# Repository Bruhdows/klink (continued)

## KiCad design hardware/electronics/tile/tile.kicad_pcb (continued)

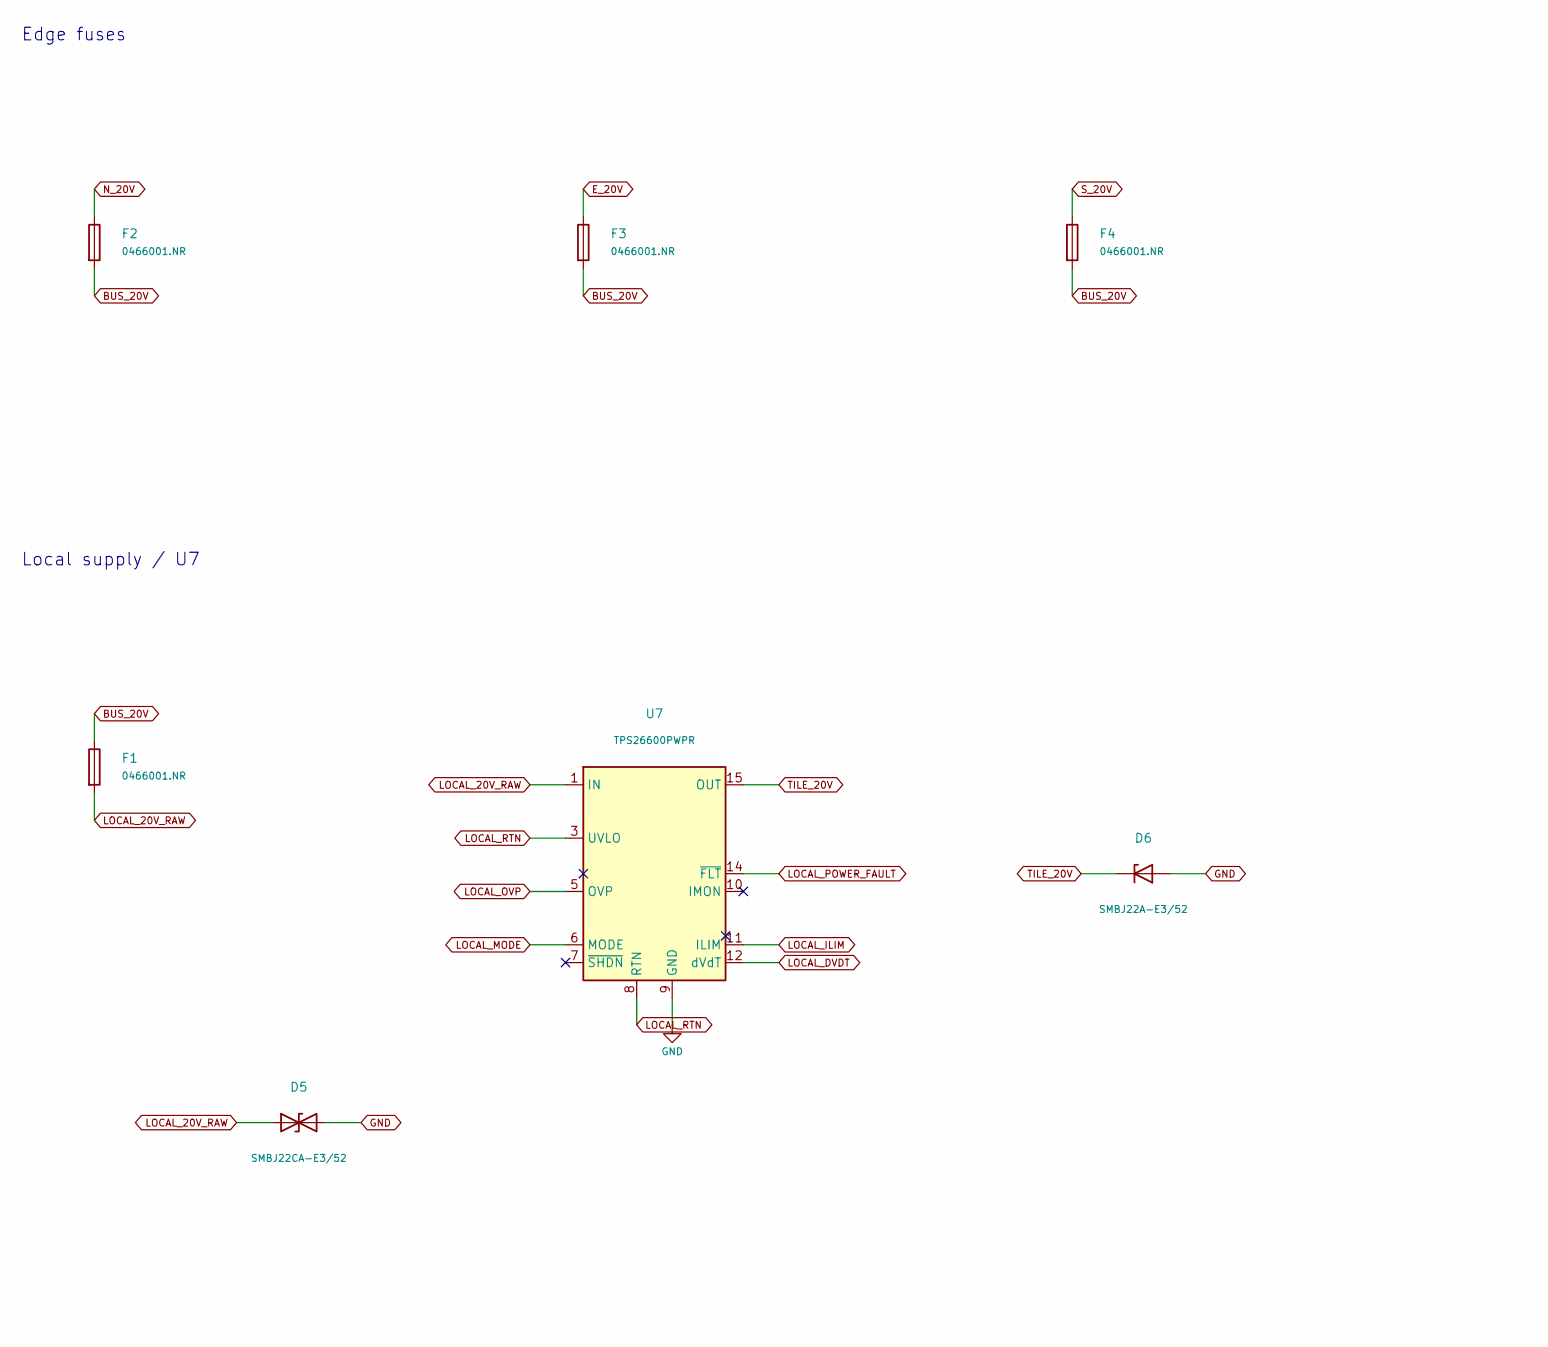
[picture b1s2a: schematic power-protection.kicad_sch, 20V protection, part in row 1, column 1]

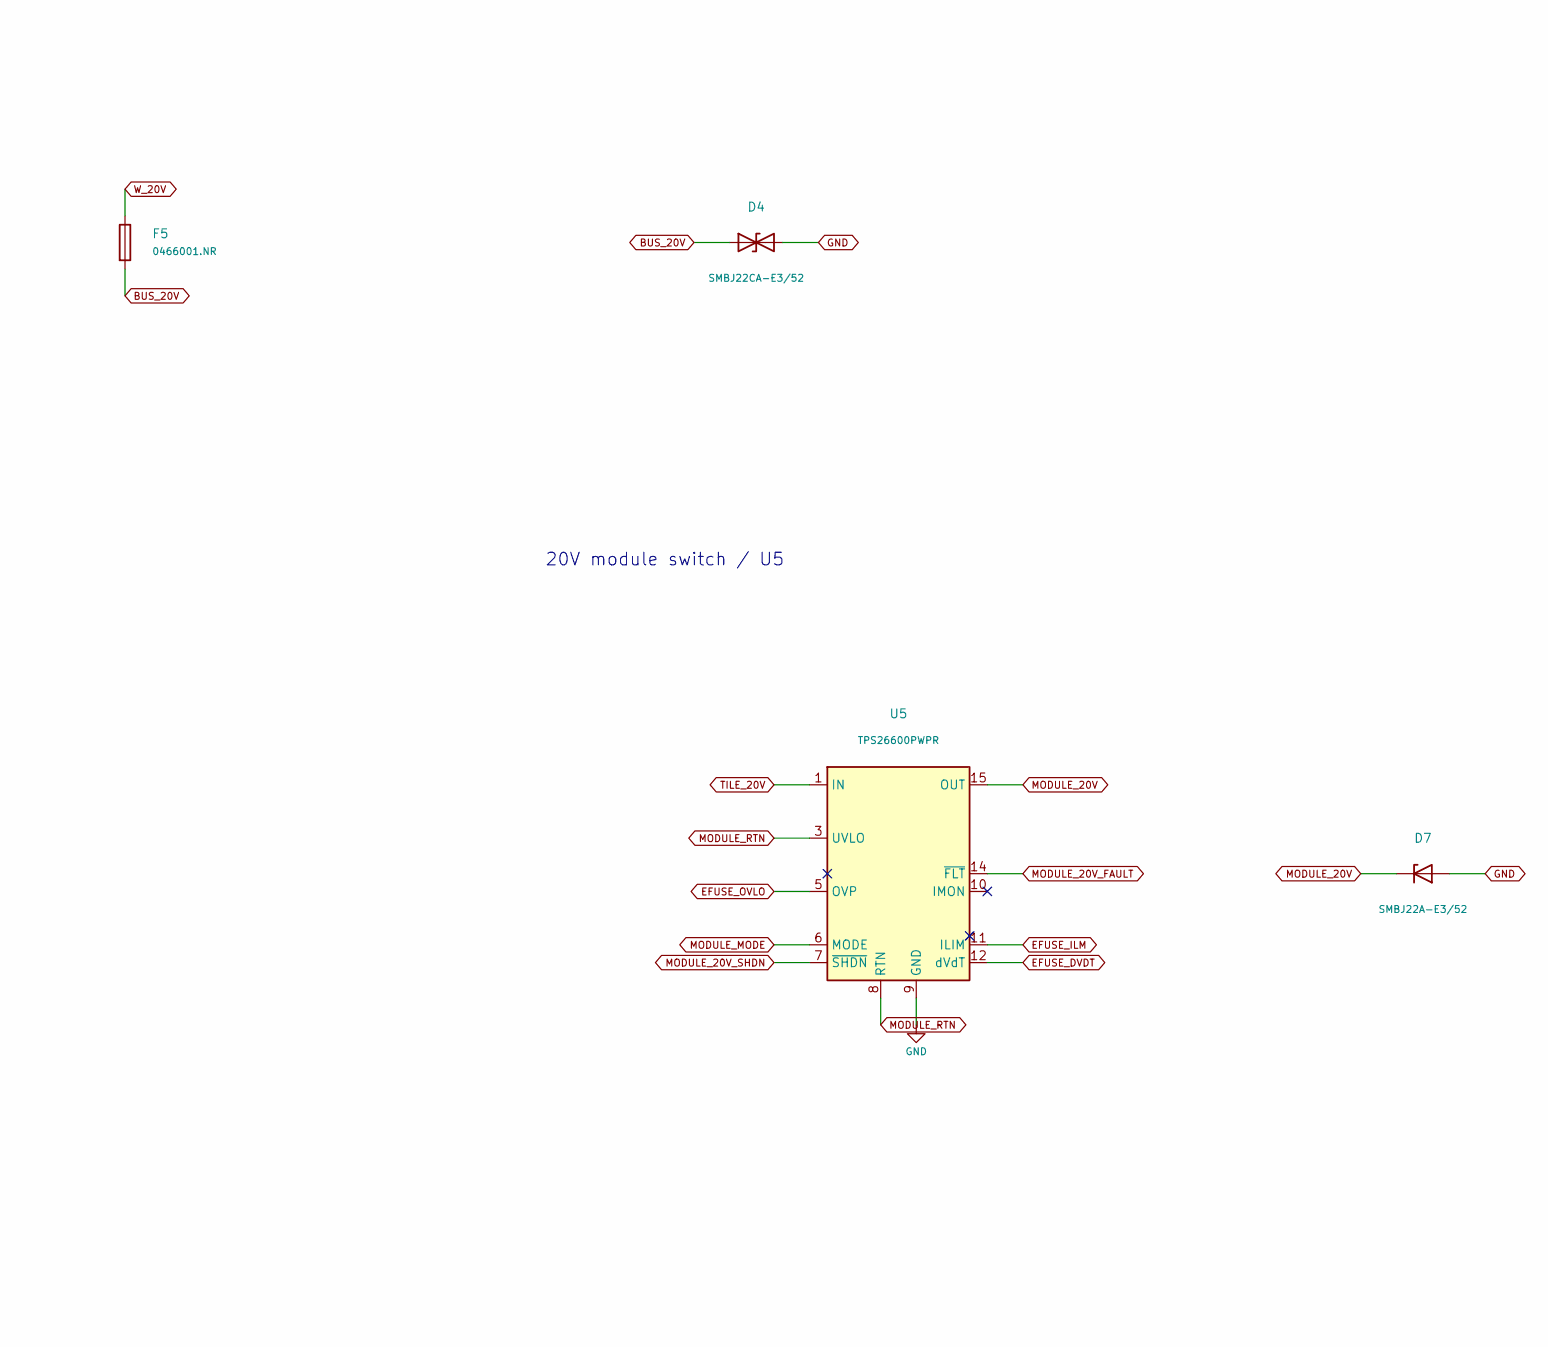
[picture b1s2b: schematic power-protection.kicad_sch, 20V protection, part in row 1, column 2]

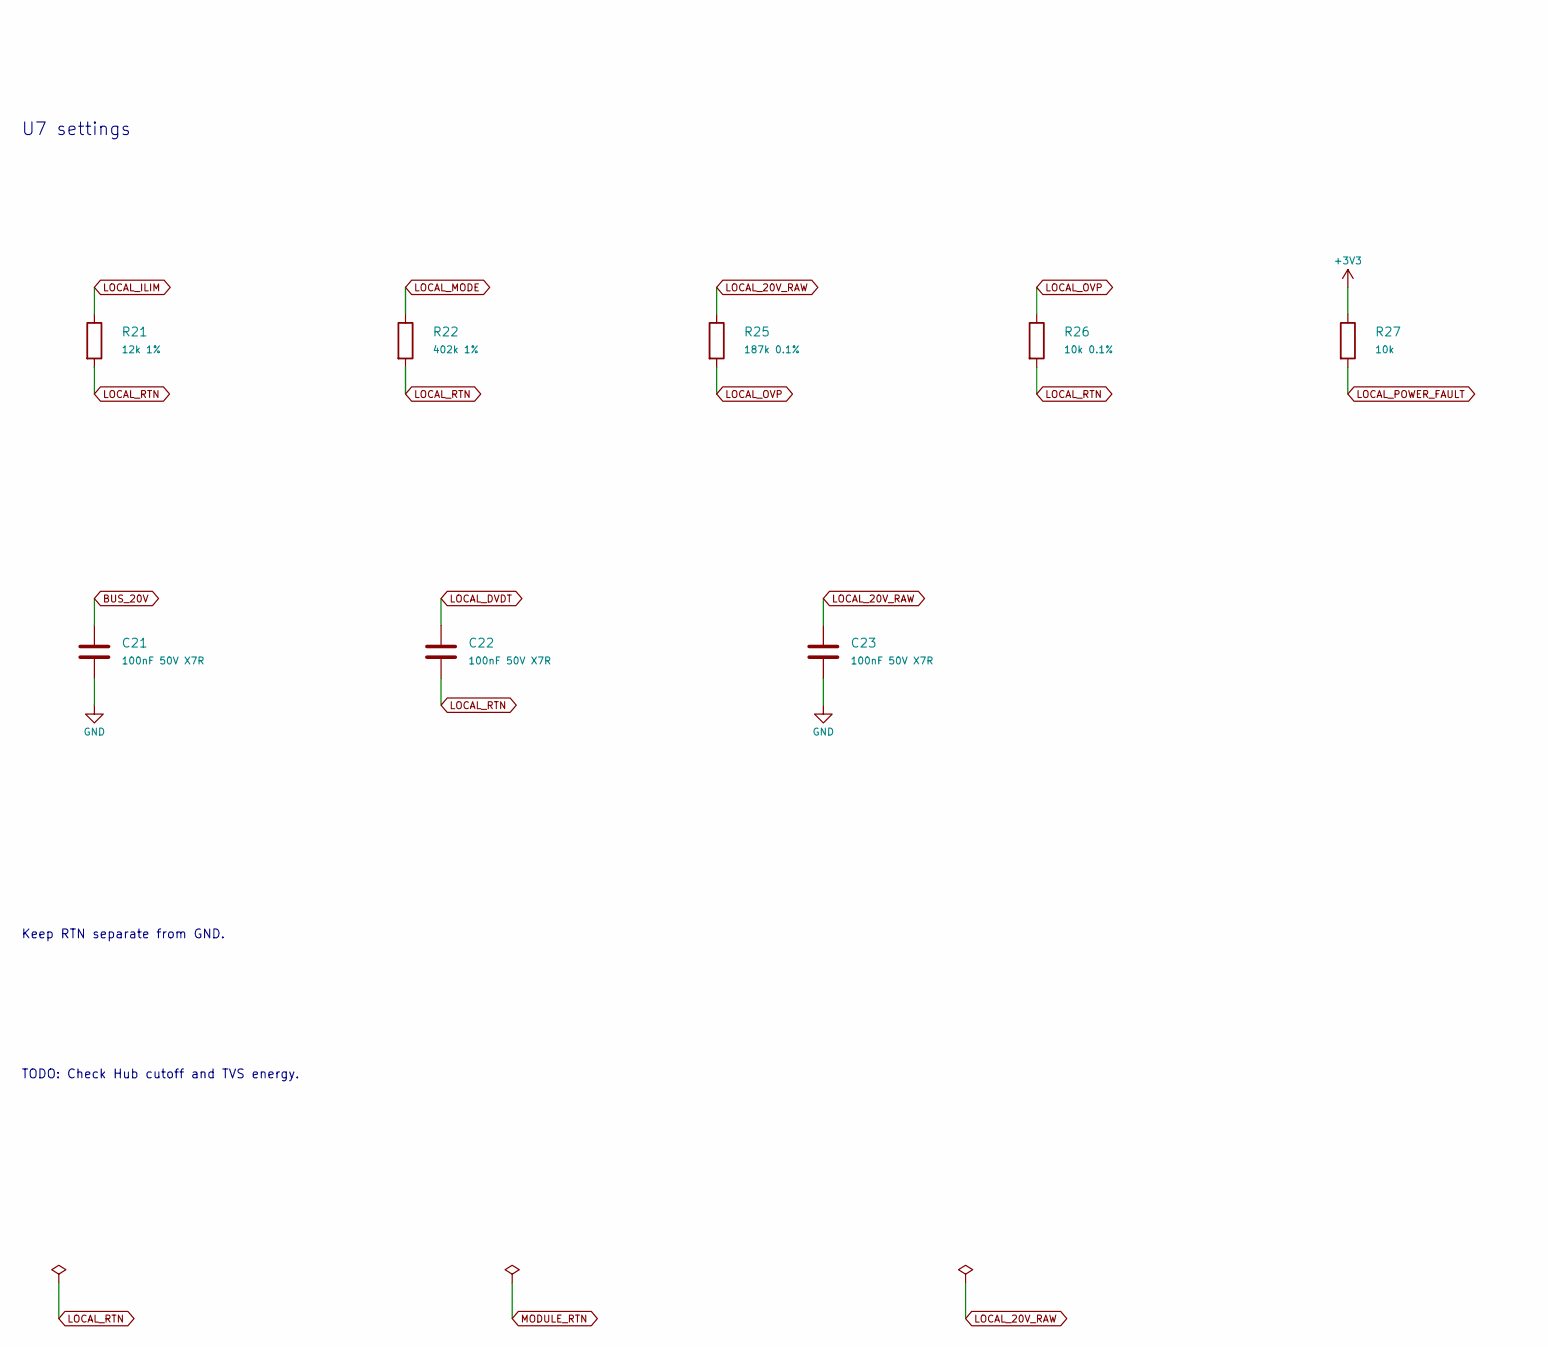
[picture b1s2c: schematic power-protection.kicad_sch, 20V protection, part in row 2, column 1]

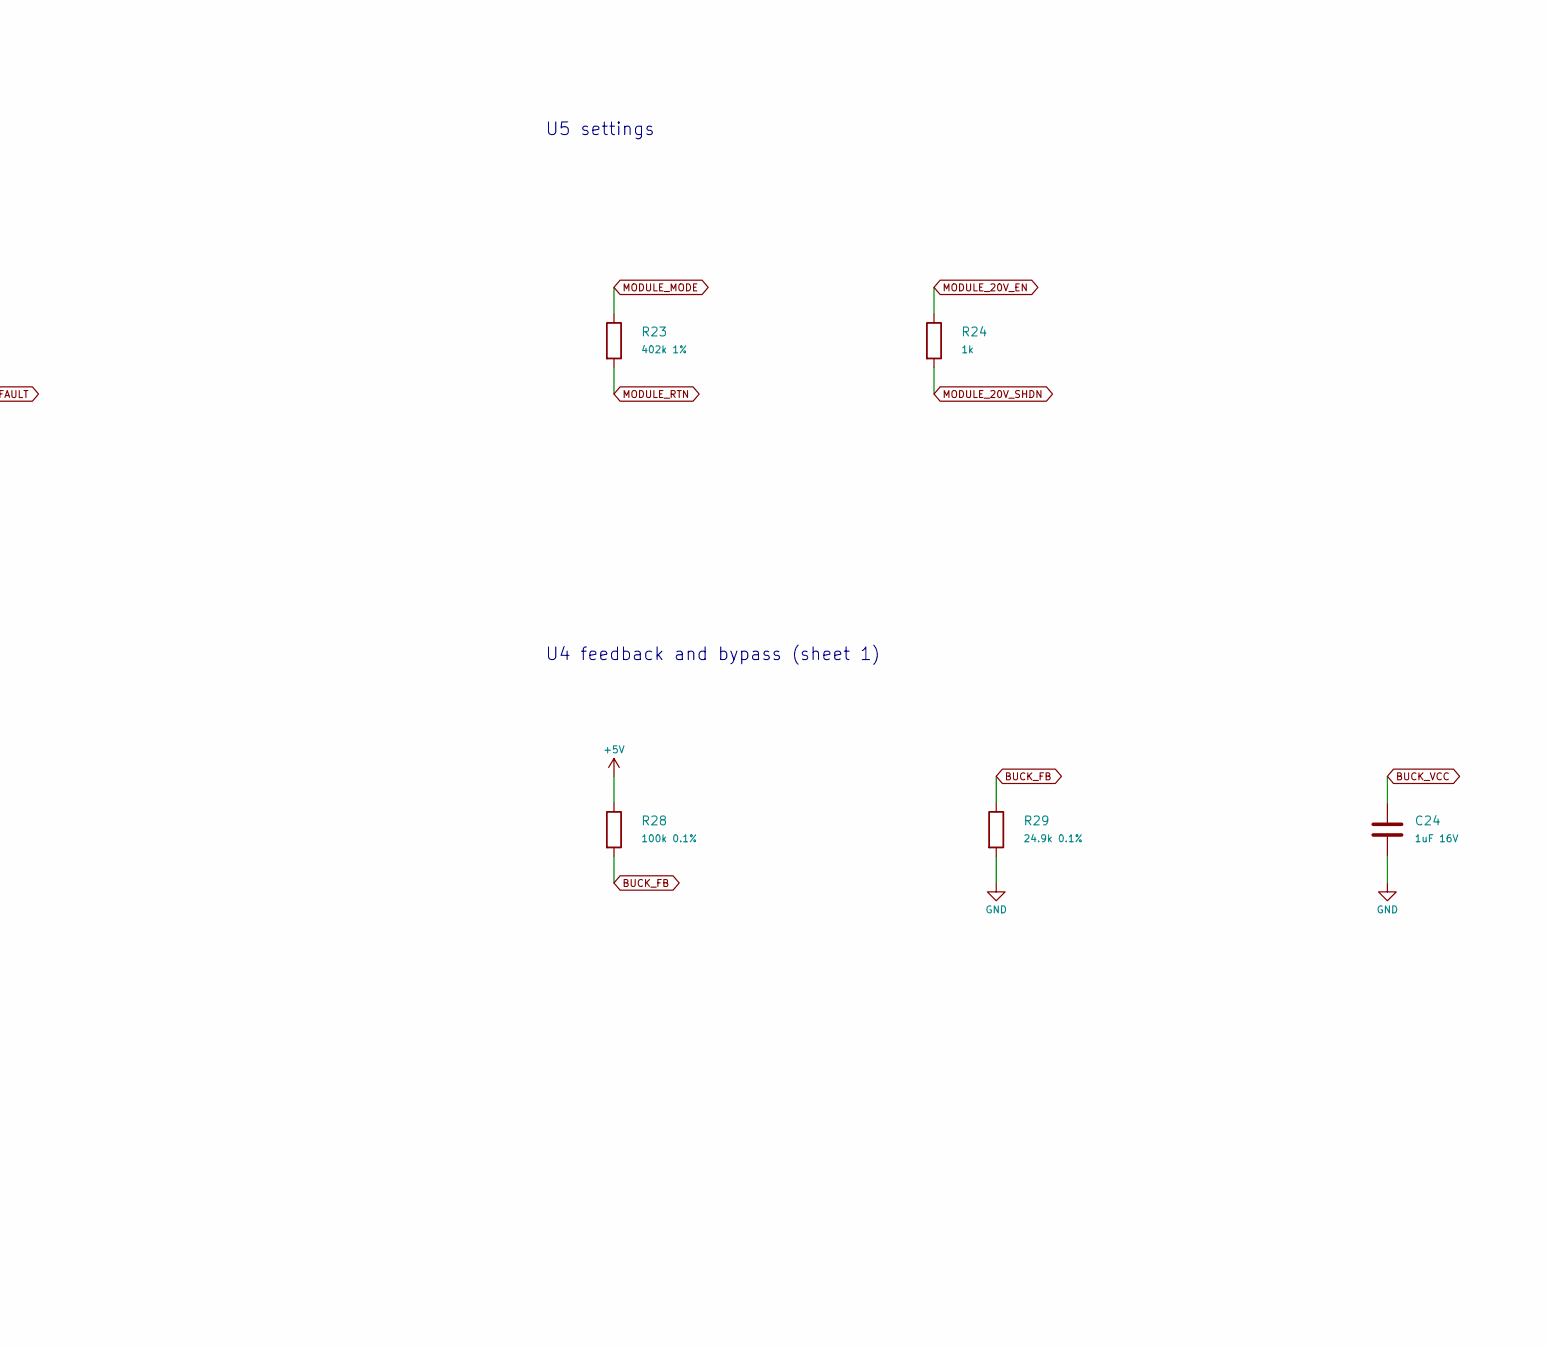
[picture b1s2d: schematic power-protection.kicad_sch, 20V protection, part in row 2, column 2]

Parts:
C21, C22, C23: 100nF 50V X7R; C_0805_2012Metric; MPN C2012X7R1H104K125AE
C24: 1uF 16V; C_0805_2012Metric; MPN C2012X7R1H105K125AB
D4, D5: SMBJ22CA-E3/52; D_SMB
D6, D7: SMBJ22A-E3/52; D_SMB
F1, F2, F3, F4, F5: 0466001.NR; Fuse_1206_3216Metric
R21: 12k 1%; R_0805_2012Metric; MPN RC0805FR-0712KL
R22, R23: 402k 1%; R_0805_2012Metric; MPN RC0805FR-07402KL
R24: 1k; R_0805_2012Metric; MPN RC0805FR-071KL
R25: 187k 0.1%; R_0805_2012Metric; MPN RT0805BRD07187KL
R26: 10k 0.1%; R_0805_2012Metric; MPN RT0805BRD0710KL
R27: 10k; R_0805_2012Metric; MPN RC0805FR-0710KL
R28: 100k 0.1%; R_0805_2012Metric; MPN RT0805BRD07100KL
R29: 24.9k 0.1%; R_0805_2012Metric; MPN RT0805BRD0724K9L
U5, U7: TPS26600PWPR; TI_PWP0016A_Mask3.3x3.3

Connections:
+3V3: R27.1; also elsewhere on the board
+5V: R28.1; also elsewhere on the board
BUCK_FB: R28.2, R29.1; also elsewhere on the board
BUCK_VCC: C24.1; also elsewhere on the board
BUS_20V: C21.1, D4.1 (A1), F1.1, F2.2, F3.2, F4.2, F5.2; also elsewhere on the board
EFUSE_DVDT: U5.12 (dVdT); also elsewhere on the board
EFUSE_ILM: U5.11 (ILIM); also elsewhere on the board
EFUSE_OVLO: U5.5 (OVP); also elsewhere on the board
E_20V: F3.1
GND: C21.2, C23.2, C24.2, D4.2 (A2), D5.2 (A2), D6.2 (A), D7.2 (A), R29.2, U5.9 (GND), U7.9 (GND); also elsewhere on the board
LOCAL_20V_RAW: C23.1, D5.1 (A1), F1.2, R25.1, U7.1 (IN), U7.2 (IN)
LOCAL_DVDT: C22.1, U7.12 (dVdT)
LOCAL_ILIM: R21.1, U7.11 (ILIM)
LOCAL_MODE: R22.1, U7.6 (MODE)
LOCAL_OVP: R25.2, R26.1, U7.5 (OVP)
LOCAL_POWER_FAULT: R27.2, U7.14 (~FLT); also elsewhere on the board
LOCAL_RTN: C22.2, R21.2, R22.2, R26.2, U7.3 (UVLO), U7.8 (RTN), U7.17 (RTN)
MODULE_20V: D7.1 (K), U5.15 (OUT), U5.16 (OUT); also elsewhere on the board
MODULE_20V_EN: R24.1; also elsewhere on the board
MODULE_20V_FAULT: U5.14 (~FLT); also elsewhere on the board
MODULE_20V_SHDN: R24.2, U5.7 (~SHDN); also elsewhere on the board
MODULE_MODE: R23.1, U5.6 (MODE)
MODULE_RTN: R23.2, U5.3 (UVLO), U5.8 (RTN), U5.17 (RTN); also elsewhere on the board
N_20V: F2.1
S_20V: F4.1
TILE_20V: D6.1 (K), U5.1 (IN), U5.2 (IN), U7.15 (OUT), U7.16 (OUT); also elsewhere on the board
W_20V: F5.1

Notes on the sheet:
Edge fuses
Local supply / U7
20V module switch / U5
U7 settings
U5 settings
U4 feedback and bypass (sheet 1)
Keep RTN separate from GND.
TODO: Check Hub cutoff and TVS energy.

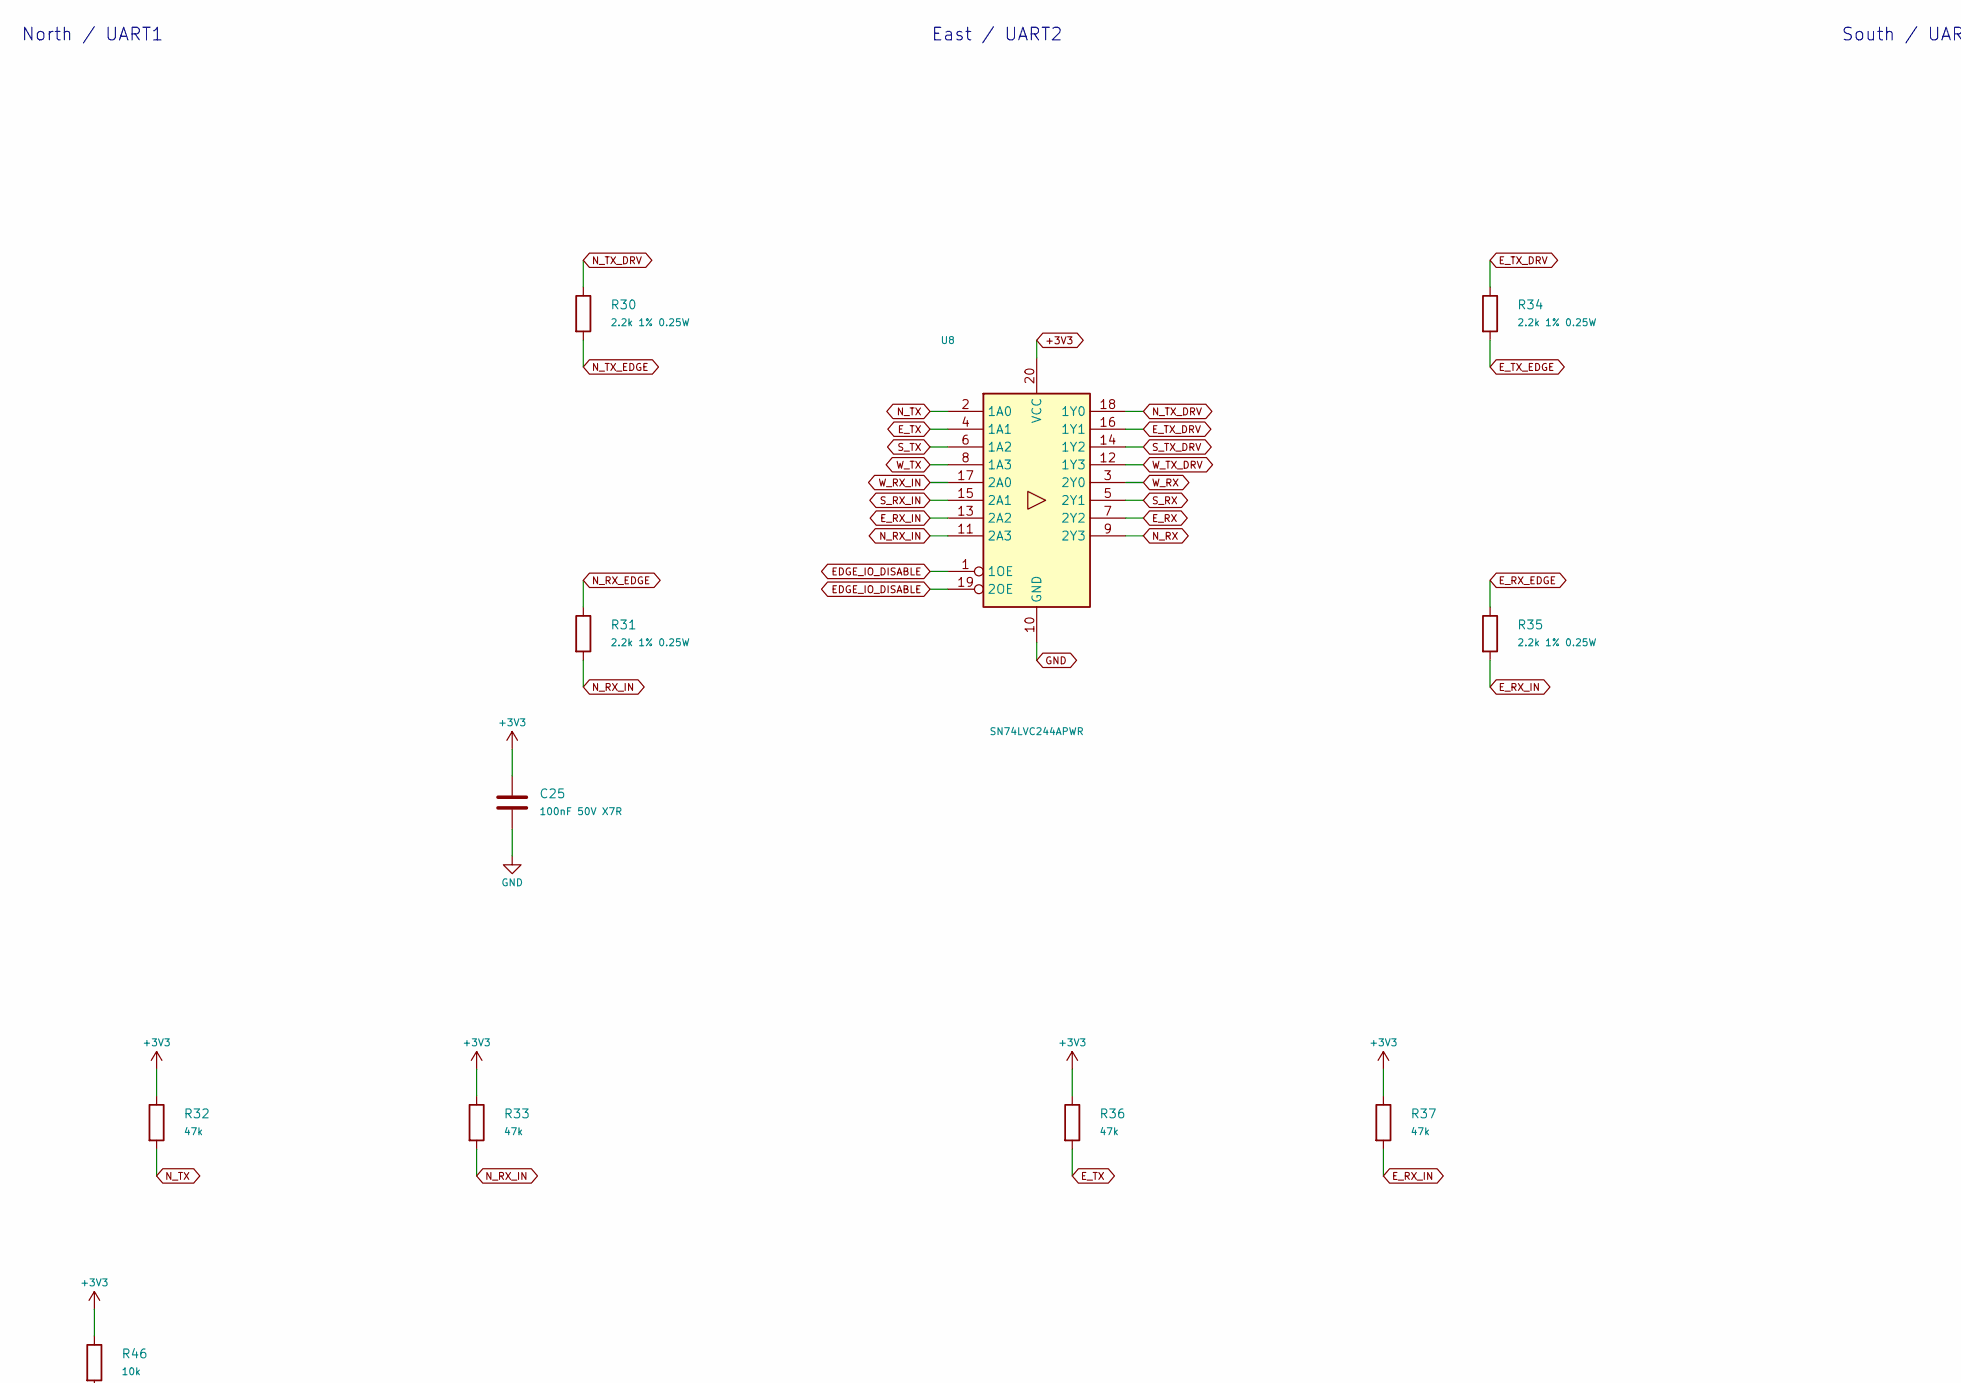
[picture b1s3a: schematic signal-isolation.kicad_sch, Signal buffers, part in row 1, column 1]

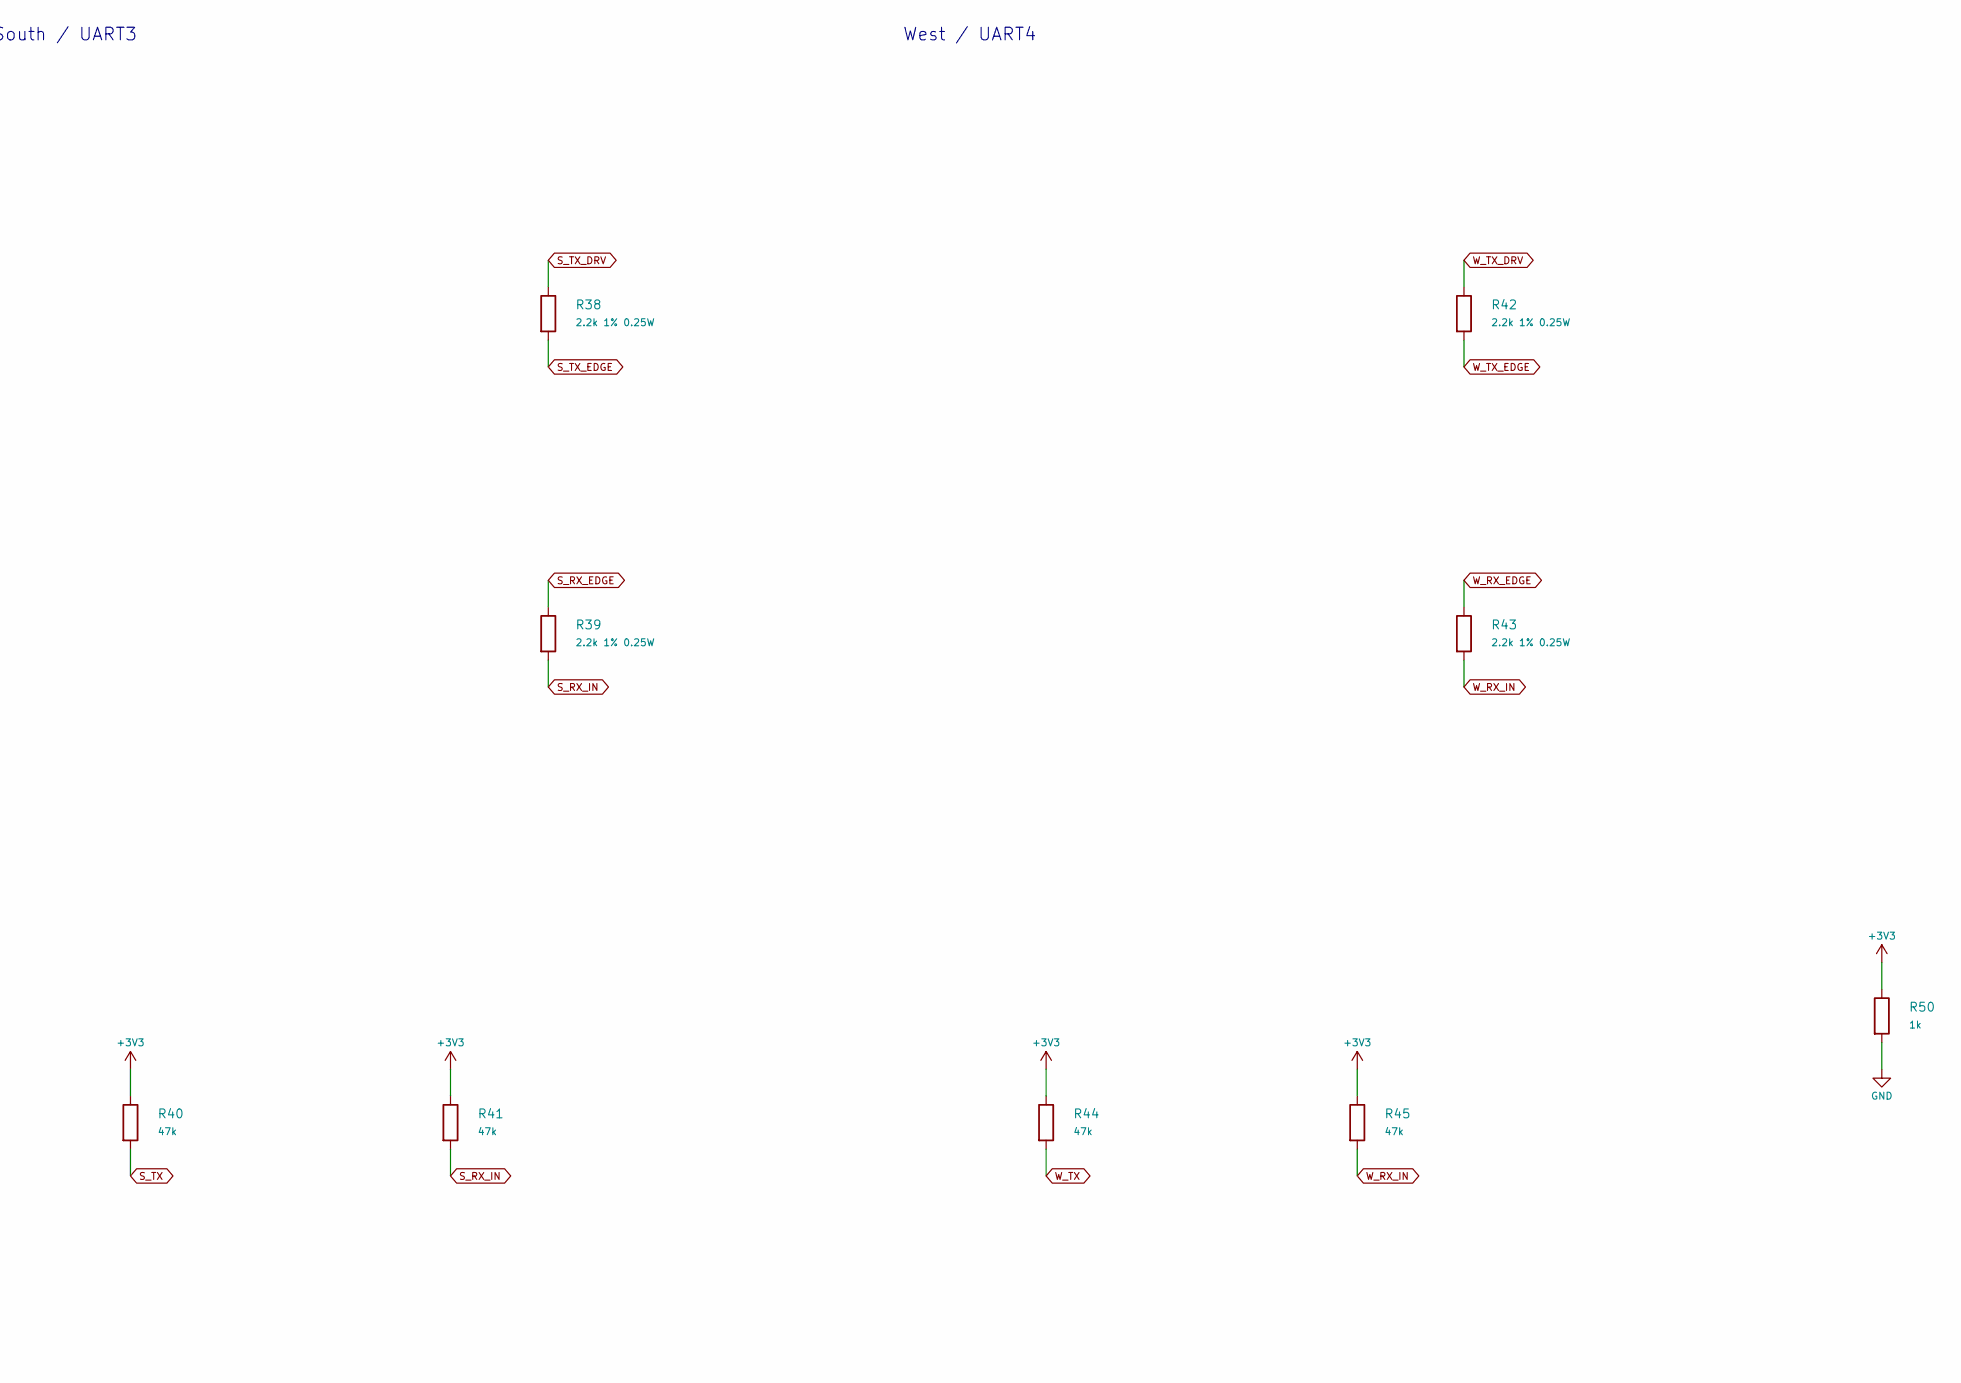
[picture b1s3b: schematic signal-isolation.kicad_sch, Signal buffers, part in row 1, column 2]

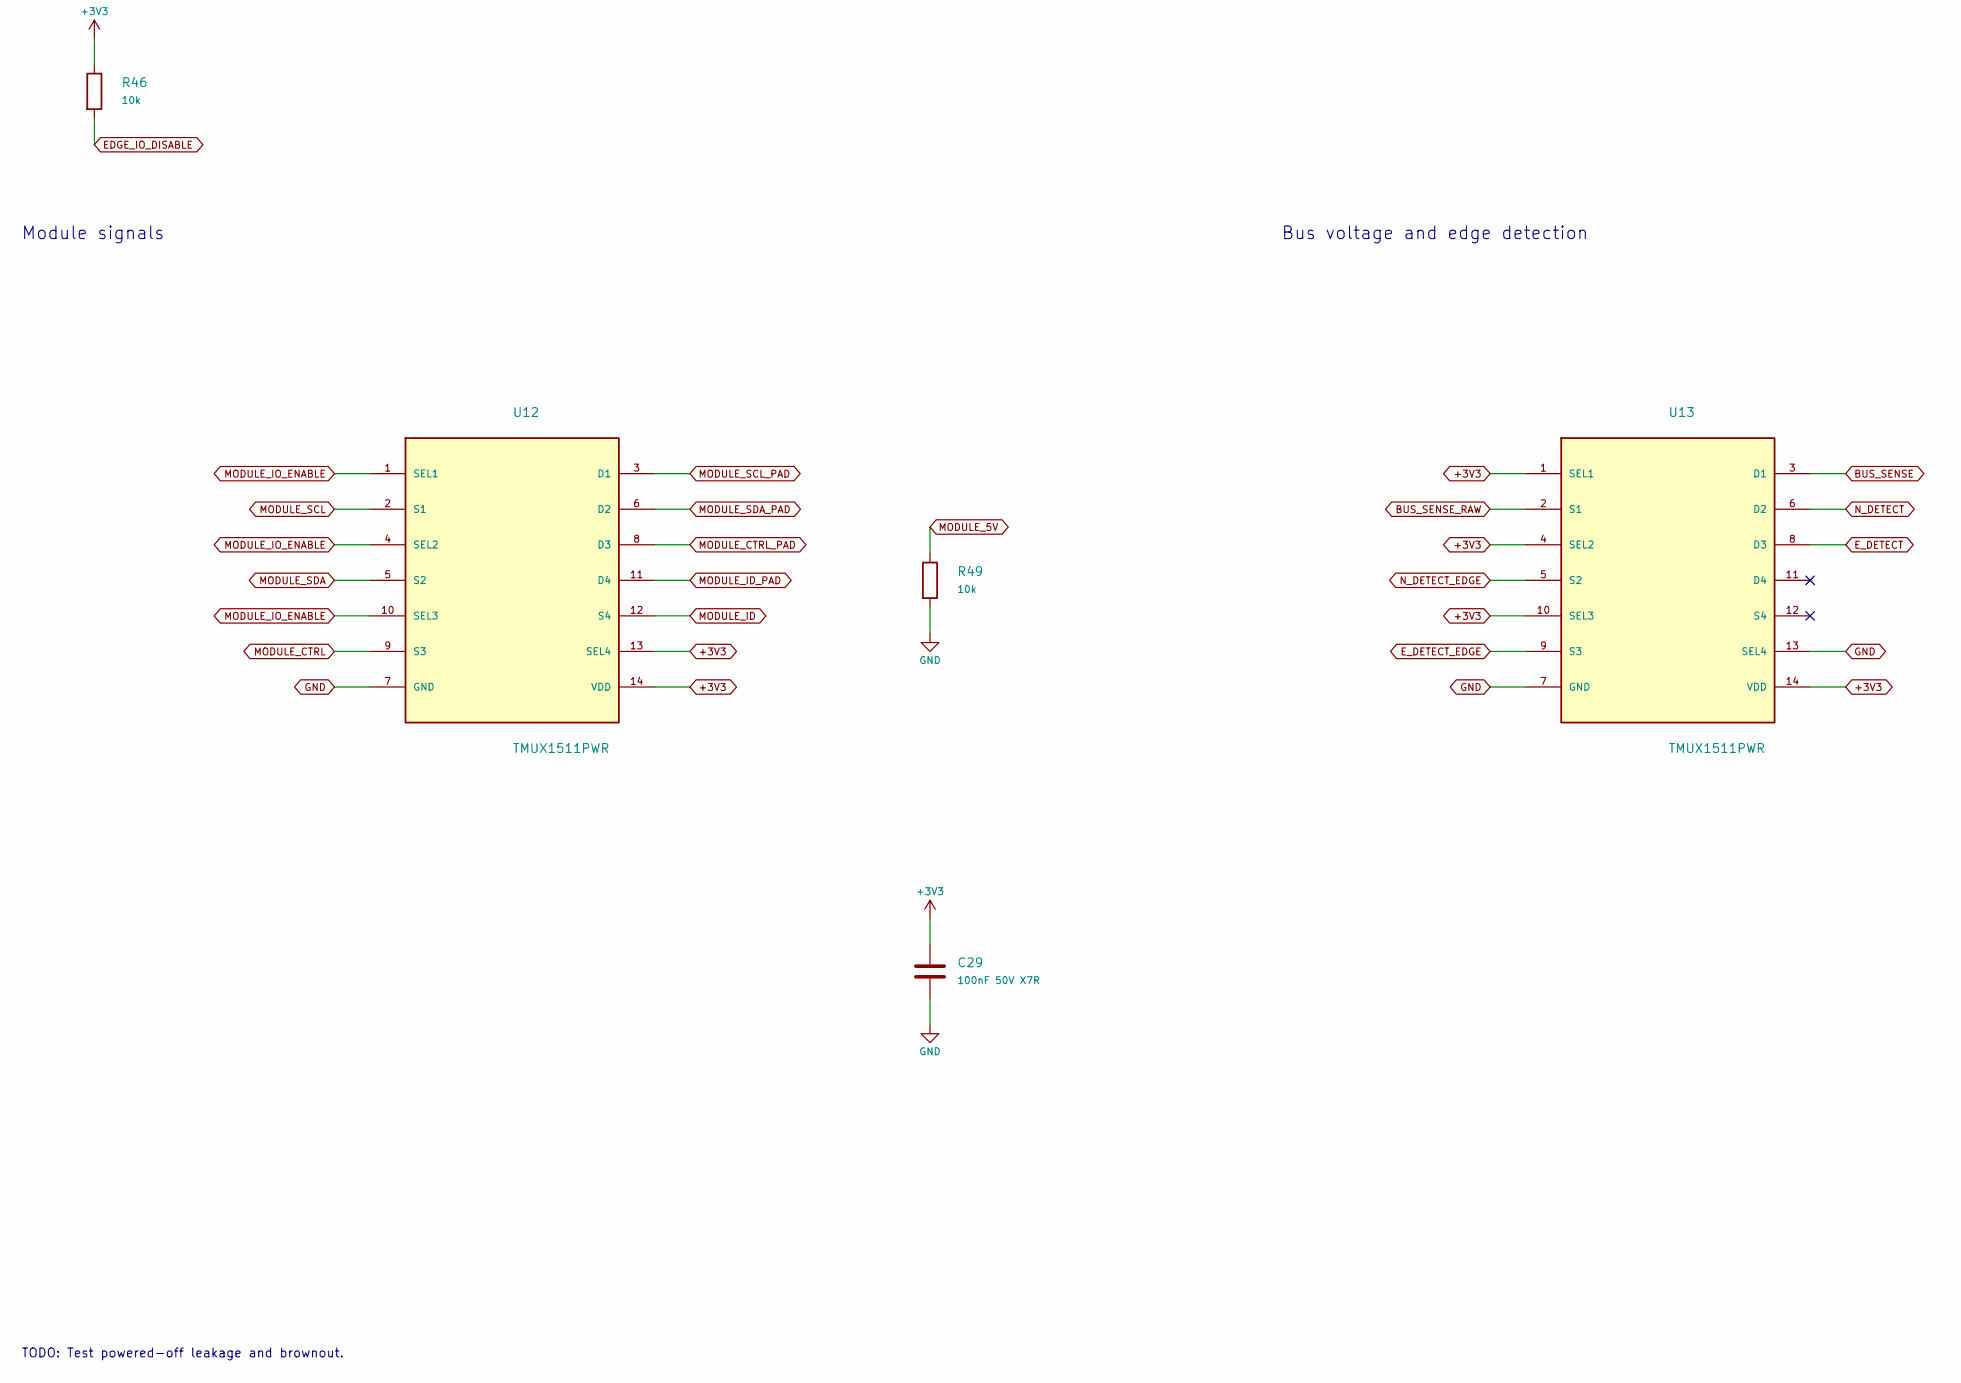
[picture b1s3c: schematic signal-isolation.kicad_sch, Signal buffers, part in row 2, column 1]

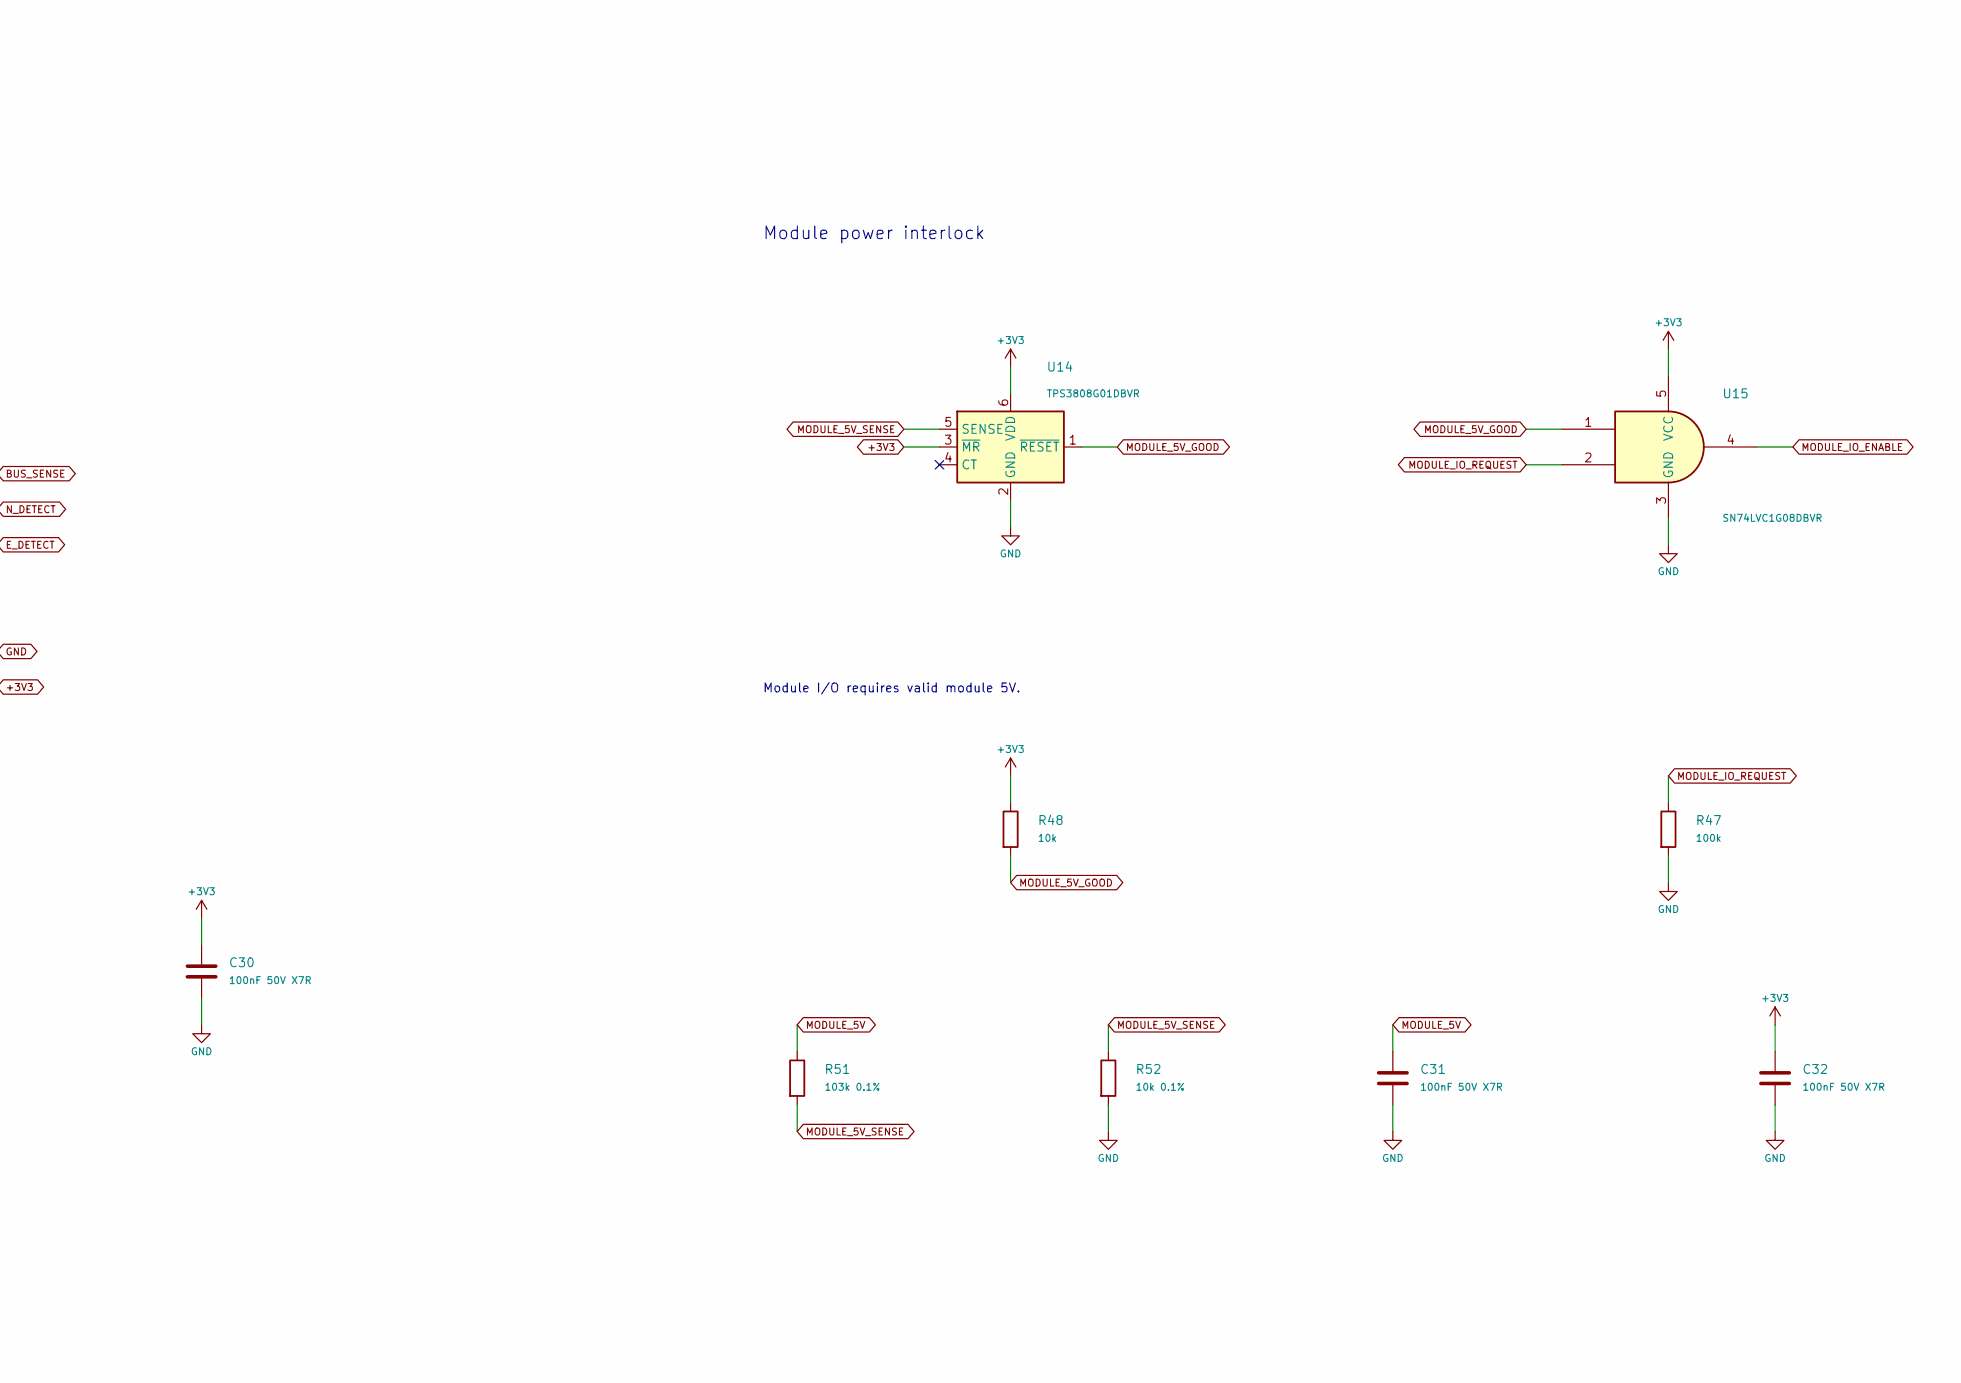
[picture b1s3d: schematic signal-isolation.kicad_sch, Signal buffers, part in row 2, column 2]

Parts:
C25, C29, C30, C31, C32: 100nF 50V X7R; C_0805_2012Metric; MPN C2012X7R1H104K125AE
R30, R31, R34, R35, R38, R39, R42, R43: 2.2k 1% 0.25W; R_1206_3216Metric; MPN RC1206FR-072K2L
R32, R33, R36, R37, R40, R41, R44, R45: 47k; R_0805_2012Metric; MPN RC0805FR-0747KL
R46, R48, R49: 10k; R_0805_2012Metric; MPN RC0805FR-0710KL
R47: 100k; R_0805_2012Metric; MPN RC0805FR-07100KL
R50: 1k; R_0805_2012Metric; MPN RC0805FR-071KL
R51: 103k 0.1%; R_0805_2012Metric; MPN RT0805BRD07103KL
R52: 10k 0.1%; R_0805_2012Metric; MPN RT0805BRD0710KL
U8: SN74LVC244APWR; TSSOP-20_4.4x6.5mm_P0.65mm; MPN SN74LVC244APWR
U12, U13: TMUX1511PWR; TSSOP-14_4.4x5mm_P0.65mm
U14: TPS3808G01DBVR; SOT-23-6
U15: SN74LVC1G08DBVR; SOT-23-5

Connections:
+3V3: C25.1, C29.1, C30.1, C32.1, R32.1, R33.1, R36.1, R37.1, R40.1, R41.1, R44.1, R45.1, R46.1, R48.1, R50.1, U8.20 (VCC), U12.13 (SEL4), U12.14 (VDD), U13.1 (SEL1), U13.4 (SEL2), U13.10 (SEL3), U13.14 (VDD), U14.3 (~MR), U14.6 (VDD), U15.5 (VCC); also elsewhere on the board
BUS_SENSE: U13.3 (D1); also elsewhere on the board
BUS_SENSE_RAW: U13.2 (S1); also elsewhere on the board
EDGE_IO_DISABLE: R46.2, U8.1 (1OE), U8.19 (2OE); also elsewhere on the board
E_DETECT: U13.8 (D3); also elsewhere on the board
E_DETECT_EDGE: U13.9 (S3); also elsewhere on the board
E_RX: U8.7 (2Y2); also elsewhere on the board
E_RX_EDGE: R35.1
E_RX_IN: R35.2, R37.2, U8.13 (2A2)
E_TX: R36.2, U8.4 (1A1); also elsewhere on the board
E_TX_DRV: R34.1, U8.16 (1Y1)
E_TX_EDGE: R34.2
GND: C25.2, C29.2, C30.2, C31.2, C32.2, R47.2, R49.2, R50.2, R52.2, U8.10 (GND), U12.7 (GND), U13.7 (GND), U13.13 (SEL4), U14.2 (GND), U15.3 (GND); also elsewhere on the board
MODULE_5V: C31.1, R49.1, R51.1; also elsewhere on the board
MODULE_5V_GOOD: R48.2, U14.1 (~RESET), U15.1
MODULE_5V_SENSE: R51.2, R52.1, U14.5 (SENSE)
MODULE_CTRL: U12.9 (S3); also elsewhere on the board
MODULE_CTRL_PAD: U12.8 (D3)
MODULE_ID: U12.12 (S4); also elsewhere on the board
MODULE_ID_PAD: U12.11 (D4)
MODULE_IO_ENABLE: U12.1 (SEL1), U12.4 (SEL2), U12.10 (SEL3), U15.4
MODULE_IO_REQUEST: R47.1, U15.2; also elsewhere on the board
MODULE_SCL: U12.2 (S1); also elsewhere on the board
MODULE_SCL_PAD: U12.3 (D1)
MODULE_SDA: U12.5 (S2); also elsewhere on the board
MODULE_SDA_PAD: U12.6 (D2)
N_DETECT: U13.6 (D2); also elsewhere on the board
N_DETECT_EDGE: U13.5 (S2); also elsewhere on the board
N_RX: U8.9 (2Y3); also elsewhere on the board
N_RX_EDGE: R31.1
N_RX_IN: R31.2, R33.2, U8.11 (2A3)
N_TX: R32.2, U8.2 (1A0); also elsewhere on the board
N_TX_DRV: R30.1, U8.18 (1Y0)
N_TX_EDGE: R30.2
S_RX: U8.5 (2Y1); also elsewhere on the board
S_RX_EDGE: R39.1
S_RX_IN: R39.2, R41.2, U8.15 (2A1)
S_TX: R40.2, U8.6 (1A2); also elsewhere on the board
S_TX_DRV: R38.1, U8.14 (1Y2)
S_TX_EDGE: R38.2
W_RX: U8.3 (2Y0); also elsewhere on the board
W_RX_EDGE: R43.1
W_RX_IN: R43.2, R45.2, U8.17 (2A0)
W_TX: R44.2, U8.8 (1A3); also elsewhere on the board
W_TX_DRV: R42.1, U8.12 (1Y3)
W_TX_EDGE: R42.2

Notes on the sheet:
North / UART1
East / UART2
South / UART3
West / UART4
Module signals
Bus voltage and edge detection
Module power interlock
Module I/O requires valid module 5V.
TODO: Test powered-off leakage and brownout.
